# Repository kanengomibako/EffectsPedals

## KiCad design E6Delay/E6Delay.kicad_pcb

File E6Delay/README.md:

E6 Delay

[https://kanengomibako.github.io/pages/00366_E6Delay.html](https://kanengomibako.github.io/pages/00366_E6Delay.html)

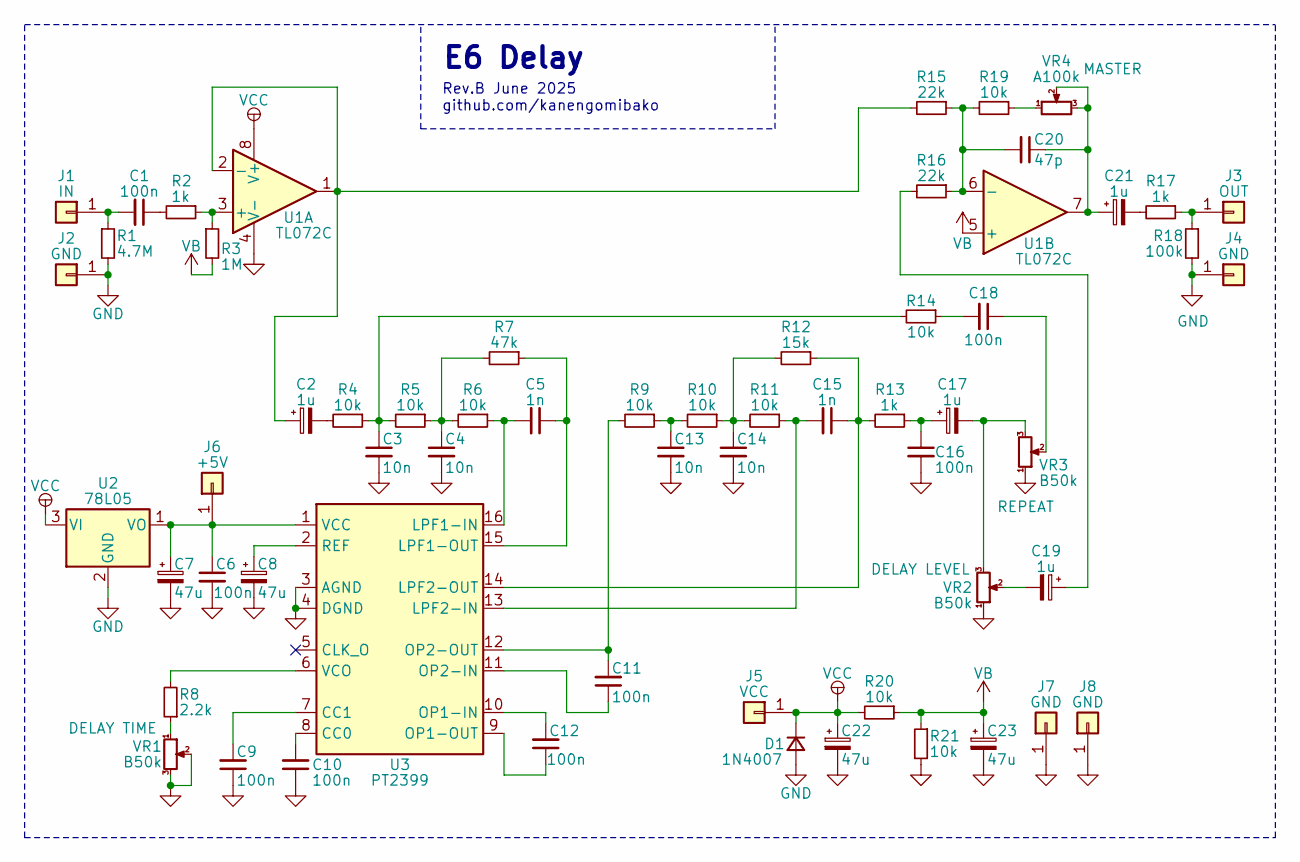
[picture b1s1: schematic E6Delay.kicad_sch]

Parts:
C1, C6, C9, C10, C11, C12, C16, C18: 100n; my_C_Rect1_P5.00mm
C2, C17, C19, C21: 1u; my_C_D5.0mm_P2.50mm
C3, C4, C13, C14: 10n; my_C_Rect1_P5.00mm
C5, C15: 1n; my_C_Rect1_P5.00mm
C7, C8, C22, C23: 47u; my_C_D5.0mm_P2.50mm
C20: 47p; my_C_Rect1_P5.00mm
D1: 1N4007; my_D_P7.62mm
J1: IN; my_WirePad_1mmDrill
J2, J4, J7, J8: GND; my_WirePad_1mmDrill
J3: OUT; my_WirePad_1mmDrill
J5: VCC; my_WirePad_1mmDrill
J6: +5V; my_WirePad_1mmDrill
R1: 4.7M; my_R_P7.62mm_Horizontal
R2, R13, R17: 1k; my_R_P7.62mm_Horizontal
R3: 1M; my_R_P7.62mm_Horizontal
R4, R5, R6, R9, R10, R11, R14, R19, R20, R21: 10k; my_R_P7.62mm_Horizontal
R7: 47k; my_R_P7.62mm_Horizontal
R8: 2.2k; my_R_P7.62mm_Horizontal
R12: 15k; my_R_P7.62mm_Horizontal
R15, R16: 22k; my_R_P7.62mm_Horizontal
R18: 100k; my_R_P7.62mm_Horizontal
U1: TL072C; DIP-8_W7.62mm_Socket
U2: 78L05; TO-92_Inline_Wide
U3: PT2399; DIP-16_W7.62mm_Socket
VR1, VR2, VR3: B50k; my_pot_5mm
VR4: A100k; my_pot_5mm

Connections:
GND: C3.2, C4.2, C6.2, C7.2, C8.2, C9.1, C10.1, C13.2, C14.2, C16.2, C22.2, C23.2, D1.2 (A), J2.1, J4.1, J7.1, J8.1, R1.2, R18.2, R21.2, U1.4 (V-), U2.2 (GND), U3.3 (AGND), U3.4 (DGND), VR1.2, VR1.3, VR2.1, VR3.1
unnamed: C1.1, R2.2
unnamed: C2.2, R4.2
unnamed: C3.1, R4.1, R5.2, R14.2
unnamed: C4.1, R5.1, R6.2, R7.2
unnamed: C13.1, R9.1, R10.2
unnamed: C14.1, R10.1, R11.2, R12.2
unnamed: C16.1, C17.1, R13.1
unnamed: C17.2, VR2.3, VR3.3
unnamed: C18.1, VR3.2
unnamed: C18.2, R14.1
unnamed: C19.1, R16.2
unnamed: C19.2, VR2.2
unnamed: C20.1, C21.1, U1.7, VR4.2, VR4.3
unnamed: C21.2, R17.2
unnamed: C1.2, J1.1, R1.1
unnamed: J3.1, R17.1, R18.1
unnamed: C6.1, C7.1, J6.1, U2.1 (VO), U3.1 (VCC)
unnamed: R8.1, VR1.1
unnamed: R19.1, VR4.1
unnamed: R2.1, R3.1, U1.3 (+)
unnamed: C2.1, R15.2, U1.1, U1.2 (-)
unnamed: C20.2, R15.1, R16.1, R19.2, U1.6 (-)
unnamed: C10.2, U3.8 (CC0)
unnamed: C9.2, U3.7 (CC1)
unnamed: C5.2, R6.1, U3.16 (LPF1-IN)
unnamed: C5.1, R7.1, U3.15 (LPF1-OUT)
unnamed: C15.2, R11.1, U3.13 (LPF2-IN)
unnamed: C15.1, R12.1, R13.2, U3.14 (LPF2-OUT)
unnamed: C12.2, U3.10 (OP1-IN)
unnamed: C12.1, U3.9 (OP1-OUT)
unnamed: C11.1, U3.11 (OP2-IN)
unnamed: C11.2, R9.2, U3.12 (OP2-OUT)
unnamed: C8.1, U3.2 (REF)
unnamed: R8.2, U3.6 (VCO)
VB: C23.1, R3.2, R20.1, R21.1, U1.5 (+)
VCC: C22.1, D1.1 (K), J5.1, R20.2, U1.8 (V+), U2.3 (VI)

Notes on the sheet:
E6 Delay
Rev.B June 2025 github.com/kanengomibako

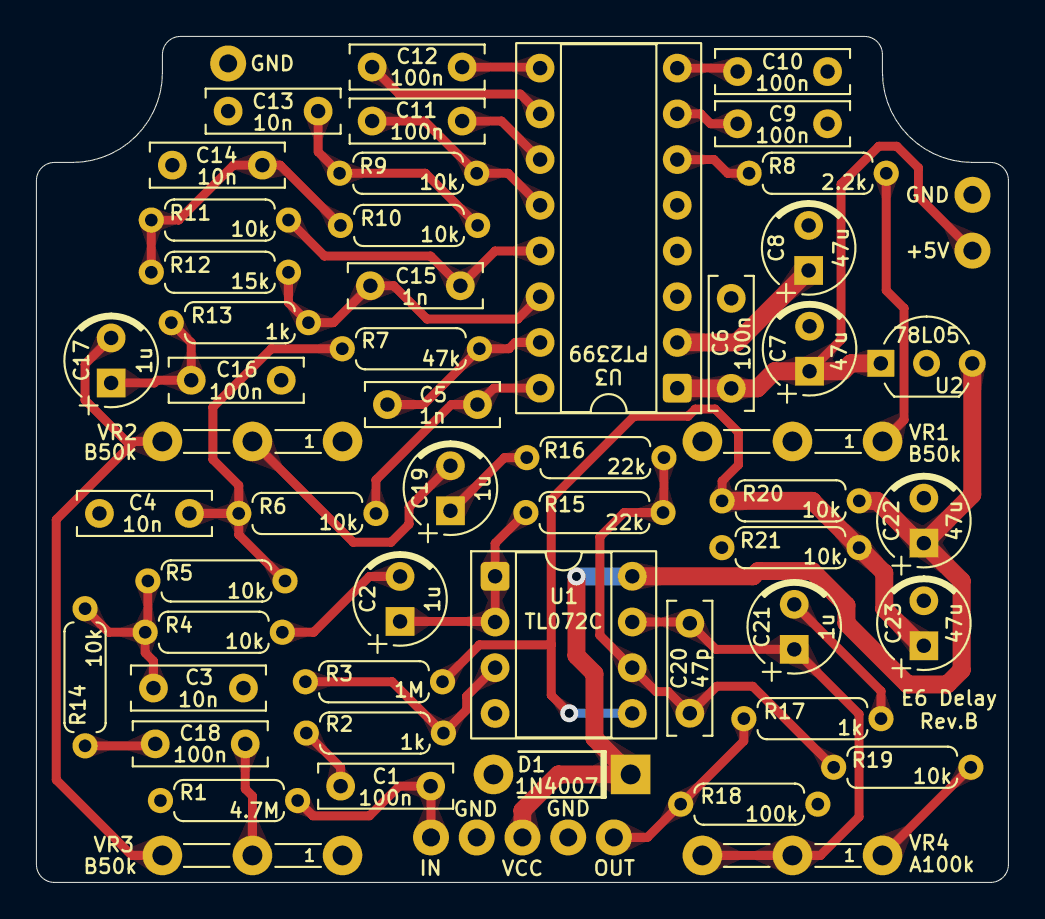
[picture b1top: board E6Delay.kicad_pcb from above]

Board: 2 copper layers, 54.0 x 47.0 mm, 60 parts (0 on the bottom side), 37 nets.

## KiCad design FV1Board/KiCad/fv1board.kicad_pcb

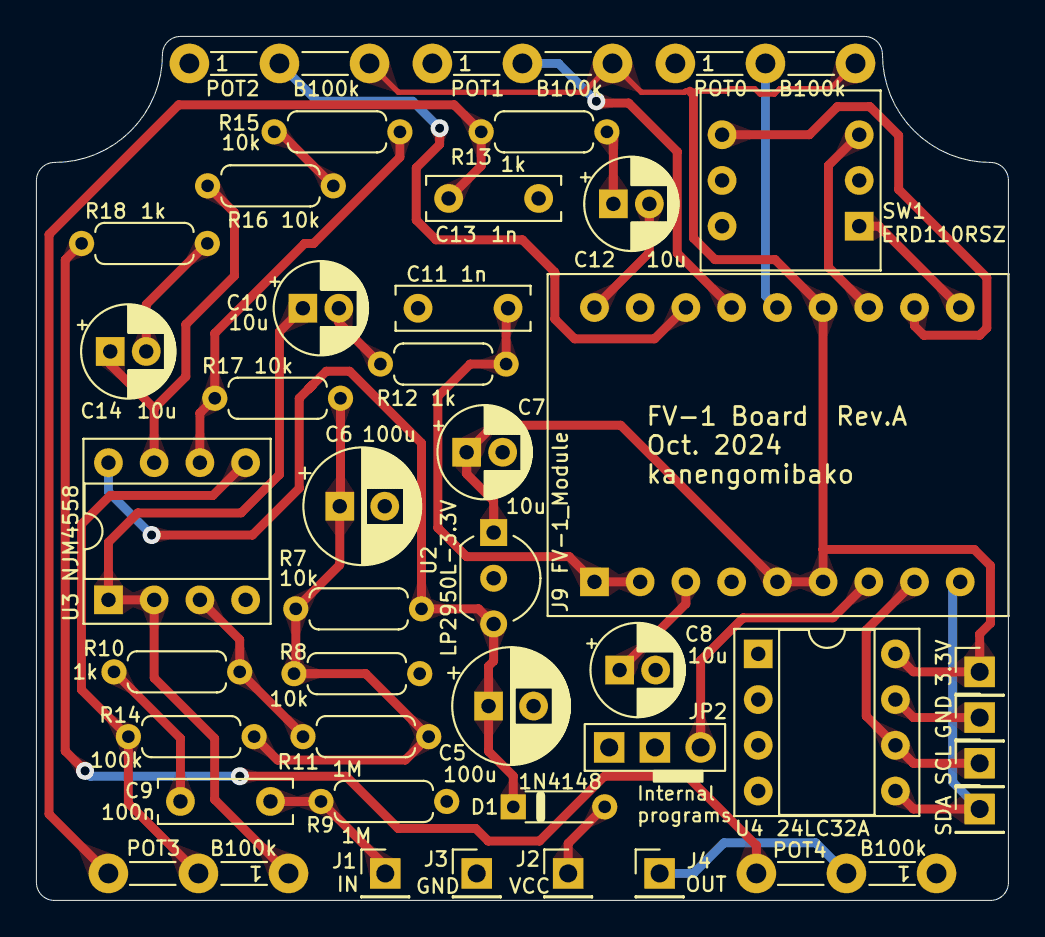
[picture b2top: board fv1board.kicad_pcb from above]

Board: 2 copper layers, 54.0 x 48.0 mm, 42 parts (0 on the bottom side), 31 nets.

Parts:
C5, C6: 100u; CP_Radial_D6.3mm_P2.50mm
C7, C8, C10, C12, C14: 10u; CP_Radial_D5.0mm_P2.00mm
C9: 100n; my_C_Rect1_P5.00mm
C11, C13: 1n; my_C_Rect1_P5.00mm
D1: 1N4148; my_D_P5.08mm_Horizontal
J1: IN; PinHeader_1x01_P2.54mm_Vertical
J2: VCC; PinHeader_1x01_P2.54mm_Vertical
J3, J8: GND; PinHeader_1x01_P2.54mm_Vertical
J4: OUT; PinHeader_1x01_P2.54mm_Vertical
J5: SDA; PinHeader_1x01_P2.54mm_Vertical
J6: SCL; PinHeader_1x01_P2.54mm_Vertical
J7: 3.3V; PinHeader_1x01_P2.54mm_Vertical
J9: FV-1_Module; DIP-18_W7.62mm
JP2: JP2; PinHeader_1x02_P2.54mm_Vertical
POT0, POT1, POT2, POT3, POT4: B100k; my_pot_5mm
R7, R8, R15, R16, R17: 10k; my_R_P7mm_Horizontal
R9, R11: 1M; my_R_P7mm_Horizontal
R10, R12, R13, R18: 1k; my_R_P7mm_Horizontal
R14: 100k; my_R_P7mm_Horizontal
SW1: ERD110RSZ; DIP-5-6_W7.62mm_Socket
U2: LP2950L-3.3V; TO-92_Inline_Wide
U3: NJM4558; DIP-8_W7.62mm_Socket
U4: 24LC32A; DIP-8_W7.62mm_Socket

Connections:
+3.3V: C7.1, J7.1, J9.5, J9.6, J9.13, POT0.3, POT1.3, POT2.3, U2.1 (VO), U4.8 (VCC)
/1_LIN: C11.1, J9.1, J9.2, R12.2
/3_MID: C8.1, J9.3
/7_T0: J9.7, JP2.2 (B)
/8_SCL: J6.1, J9.8, U4.6 (SCL)
/9_SDA: J5.1, J9.9, U4.5 (SDA)
/10_S0: J9.10, SW1.1
/11_S1: J9.11, SW1.2
/12_S2: J9.12, SW1.4
/14_POT0: J9.14, POT0.2
/15_POT1: J9.15, POT1.2
/16_POT2: J9.16, POT2.2
/18_LOUT: C12.2, J9.18
GND: C5.2, C6.2, C7.2, C8.2, C11.2, C13.2, J3.1, J8.1, J9.4, JP2.1 (A), POT0.1, POT1.1, POT2.1, POT4.1, R8.2, R9.2, SW1.C, U2.2 (GND), U3.4 (V-), U4.1 (A0), U4.2 (A1), U4.3 (A2), U4.4 (GND), U4.7 (WP)
unnamed: C9.1, R10.1
unnamed: C10.2, R12.1
unnamed: C12.1, R13.1
unnamed: C13.1, POT3.3, R13.2
unnamed: C14.1, R16.2, U3.7
unnamed: C14.2, R18.1
unnamed: D1.2 (A), J2.1
unnamed: C9.2, J1.1, R9.1
unnamed: J4.1, POT4.2
unnamed: POT4.3, R18.2
unnamed: R15.2, R16.1
unnamed: R10.2, R11.1, U3.3 (+)
unnamed: C10.1, POT3.1, U3.1, U3.2 (-)
unnamed: POT3.2, R14.1, U3.5 (+)
unnamed: R15.1, R17.2, U3.6 (-)
VB: C6.1, R7.2, R8.1, R11.2, R14.2, R17.1
VCC: C5.1, D1.1 (K), R7.1, U2.3 (VI), U3.8 (V+)

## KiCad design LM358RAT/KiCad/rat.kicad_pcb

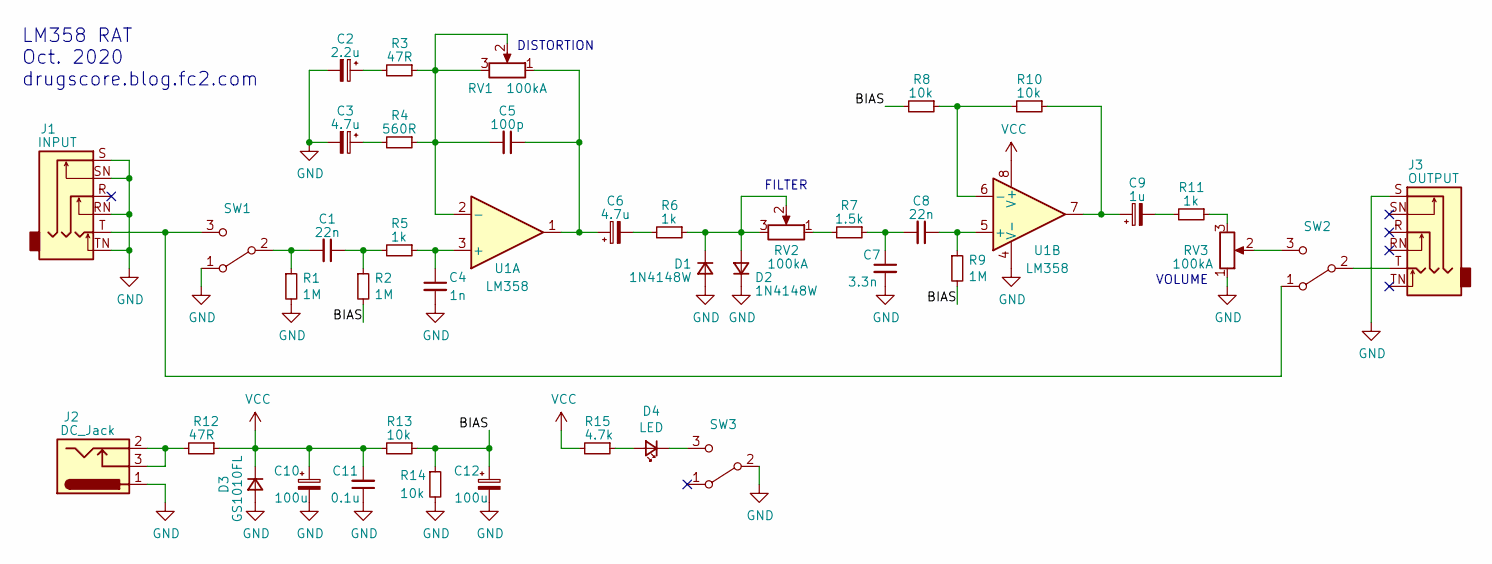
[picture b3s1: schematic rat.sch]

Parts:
C1, C8: 22n; my_C_2012(0805)_HandSoldering
C2: 2.2u; my_C_Elec_4
C3, C6: 4.7u; my_C_Elec_4
C4: 1n; my_C_1608(0603)_HandSoldering
C5: 100p; my_C_1608(0603)_HandSoldering
C7: 3.3n; my_C_1608(0603)_HandSoldering
C9: 1u; my_C_Elec_4
C10, C12: 100u; my_C_Elec_6.3
C11: 0.1u; my_C_1608(0603)_HandSoldering
D1, D2: 1N4148W; my_D_SOD-123
D3: GS1010FL; my_D_GS1010FL
D4: LED; LED_D3.0mm
J1: INPUT; my_Phone_Jack_Daier
J2: DC_Jack; my_DC_Jack
J3: OUTPUT; my_Phone_Jack_Daier
R1, R2, R9: 1M; my_R_1608(0603)_HandSoldering
R3, R12: 47R; my_R_2012(0805)_HandSoldering
R4: 560R; my_R_2012(0805)_HandSoldering
R5, R6, R11: 1k; my_R_2012(0805)_HandSoldering
R7: 1.5k; my_R_1608(0603)_HandSoldering
R8, R10, R13, R14: 10k; my_R_1608(0603)_HandSoldering
R15: 4.7k; my_R_1608(0603)_HandSoldering
RV1, RV2, RV3: 100kA; my_pot_slide_45mm_travel
SW1, SW2, SW3: SW_3PDT; my_sw_foot
U1: LM358; my_SOIC-8_3.9x4.9mm_Pitch1.27mm

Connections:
/BIAS: C12.1, R2.2, R8.2, R9.2, R13.1, R14.1
GND: C2.2, C3.2, C4.2, C7.2, C10.2, C11.1, C12.2, D1.2 (A), D2.1 (K), D3.2 (A), J1.RN, J1.S, J1.SN, J1.TN, J2.1, J3.S, R1.2, R14.2, RV3.1, SW1.1 (A), SW3.2 (B), U1.4 (V-); also elsewhere on the board
unnamed: C1.1, R2.1, R5.2
unnamed: C1.2, R1.1, SW1.2 (B)
unnamed: C2.1, R3.2
unnamed: C3.1, R4.2
unnamed: C4.1, R5.1, U1.3 (+)
unnamed: C5.1, C6.1, RV1.1, U1.1
unnamed: C5.2, R3.1, R4.1, RV1.2, RV1.3, U1.2 (-)
unnamed: C6.2, R6.2
unnamed: C7.1, C8.2, R7.1
unnamed: C8.1, R9.1, U1.5 (+)
unnamed: C9.1, R10.1, U1.7
unnamed: C9.2, R11.2
unnamed: D1.1 (K), D2.2 (A), R6.1, RV2.2, RV2.3
unnamed: D4.1 (K), SW3.3 (C)
unnamed: D4.2 (A), R15.1
unnamed: J1.T, SW1.3 (C), SW2.1 (A)
unnamed: J2.2, J2.3, R12.2
unnamed: J3.T, SW2.2 (B)
unnamed: R7.2, RV2.1
unnamed: R8.1, R10.2, U1.6 (-)
unnamed: R11.1, RV3.3
unnamed: RV3.2, SW2.3 (C)
VCC: C10.1, C11.2, D3.1 (K), R12.1, R13.2, R15.2, U1.8 (V+)

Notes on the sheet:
DISTORTION
LM358 RAT Oct. 2020 drugscore.blog.fc2.com
FILTER
VOLUME

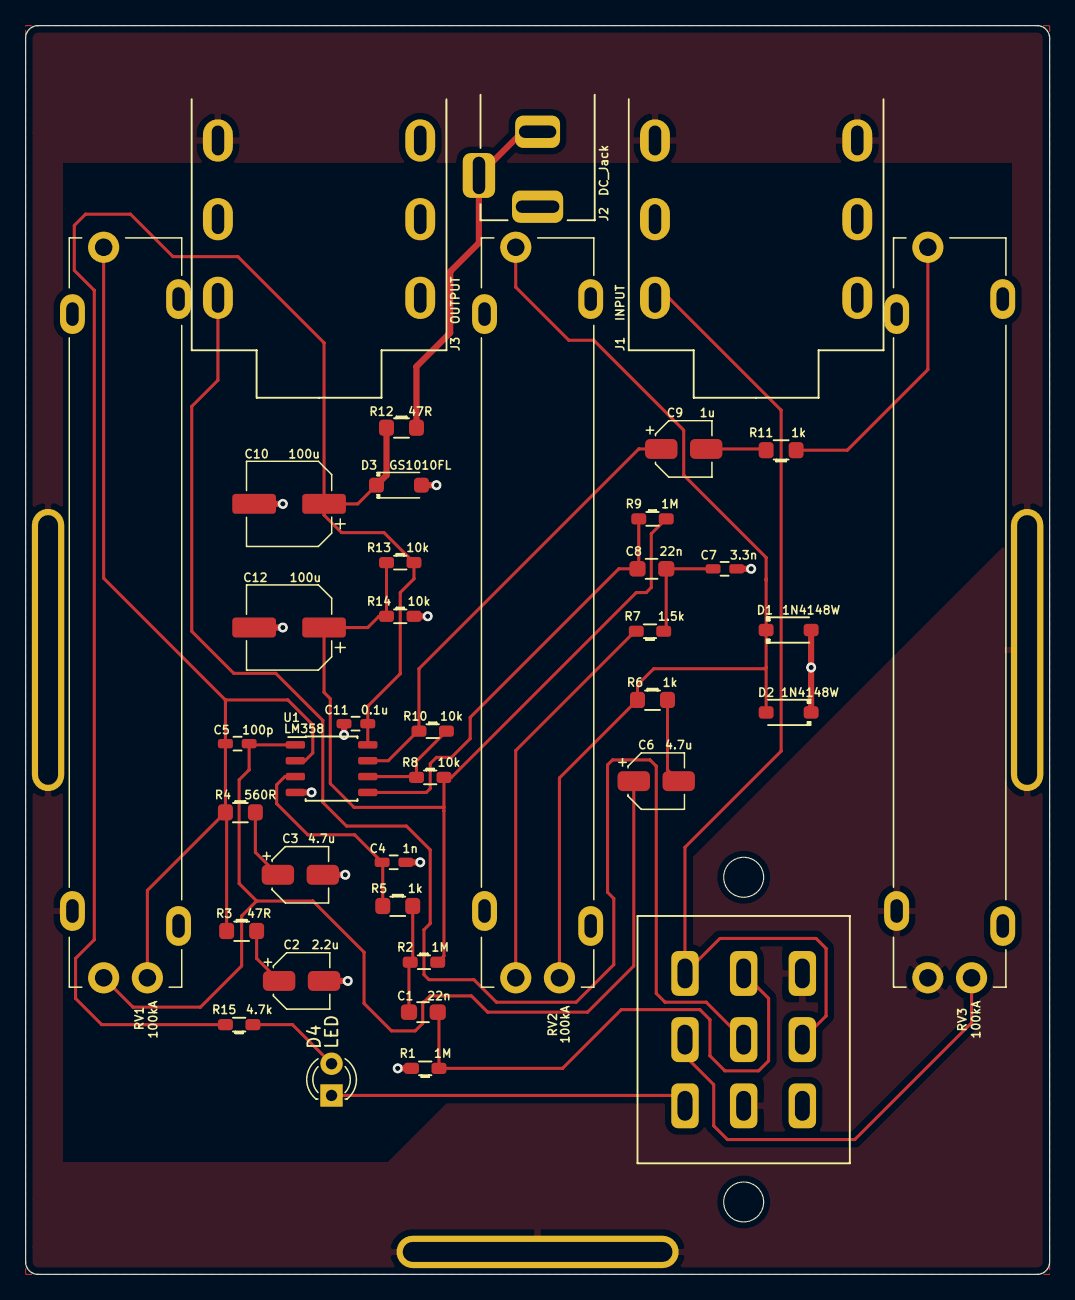
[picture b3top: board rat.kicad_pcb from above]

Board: 2 copper layers, 82.0 x 100.0 mm, 46 parts (0 on the bottom side), 25 nets.

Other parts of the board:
*: *; MountingHole_3.2mm_M3
*#2: *; MountingHole_3.2mm_M3
*#3, *#4, *#5: s; my_SmallPad_0-8mmDrill

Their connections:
GND: *#3.1, *#4.1, *#5.1; also elsewhere on the board
